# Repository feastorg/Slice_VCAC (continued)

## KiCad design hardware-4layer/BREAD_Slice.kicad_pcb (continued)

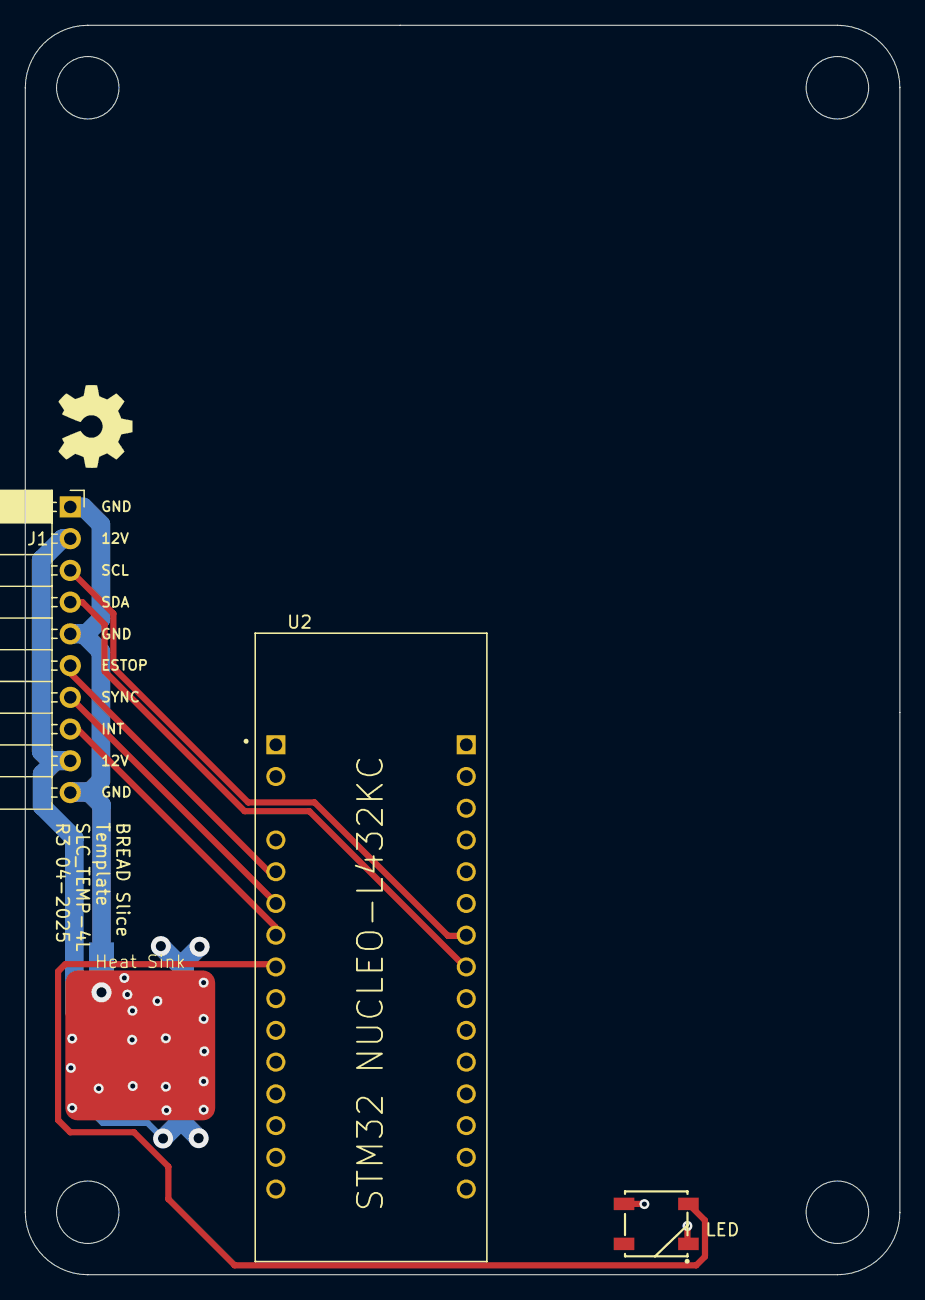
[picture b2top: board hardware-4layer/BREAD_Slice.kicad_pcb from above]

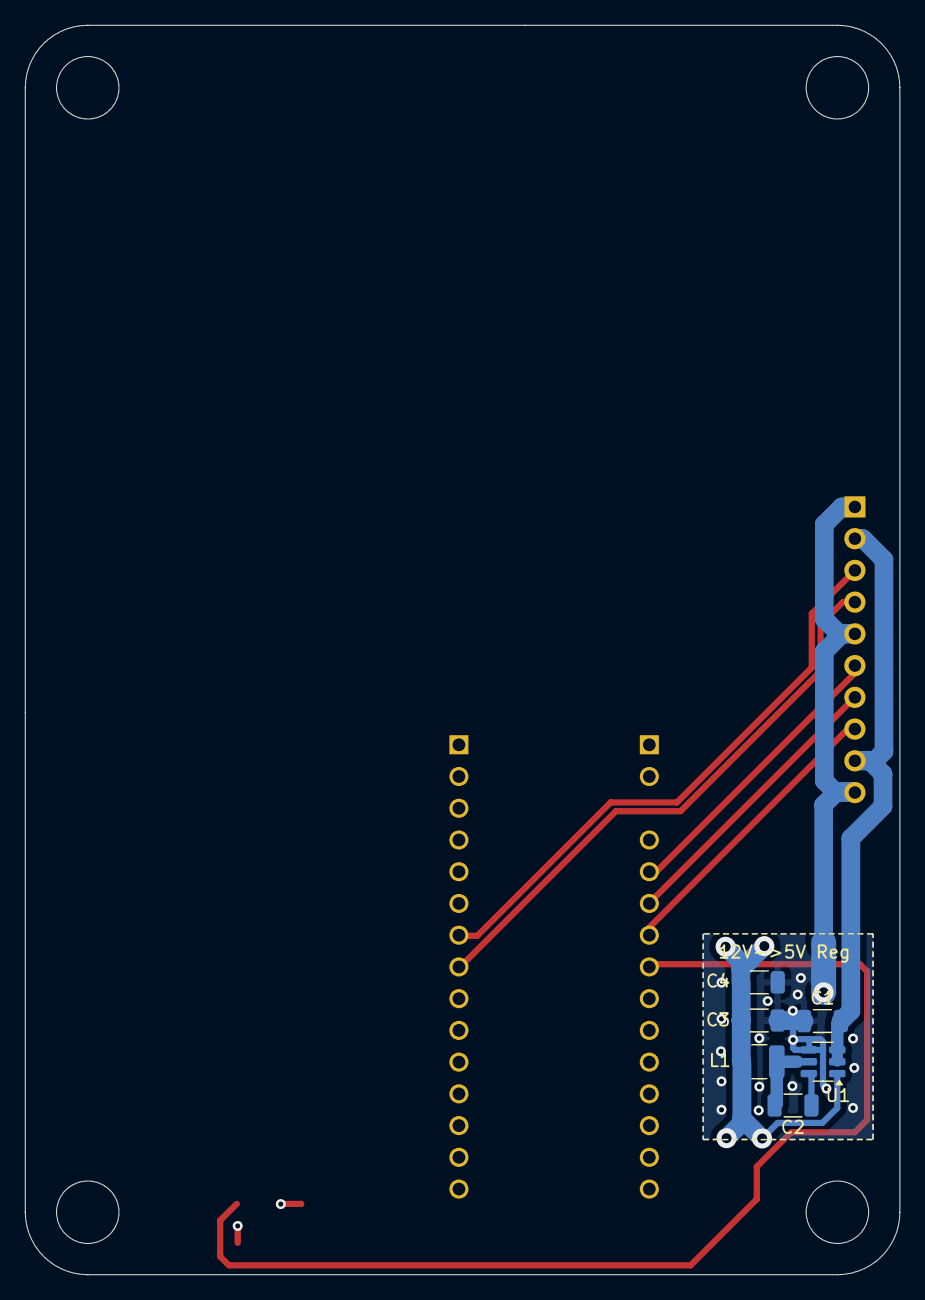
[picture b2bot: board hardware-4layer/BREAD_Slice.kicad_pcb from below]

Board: 4 copper layers, 70.0 x 100.0 mm, 16 parts (7 on the bottom side), 12 nets.

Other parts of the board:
Logo1: Logo_Open_Hardware_Small; OSHW-Symbol_6.7x6mm_SilkScreen

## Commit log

2025-04-19 initial commit after split of ac and dc
2025-04-19 minor tweaks
2025-05-04 finalized pcb
2025-05-04 added some part to dump
2026-05-20 Add slice.yaml manifest (schema v1.0)
2026-05-24 Add KiBot/docs pipeline
2026-05-24 📄 KiBot index + board renders (auto)
2026-05-24 Update TODO with CI results
2026-05-24 Standardize TODO.md with Pass 1/Pass 2 structure
